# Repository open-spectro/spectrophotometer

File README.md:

# Learning spectrophotometry

## Introduction

You can find very expensive and powerful 
spectrophotometer on the market but for teaching they are most
of the time a black box that can not be open.

In order to be able to better teach the technique we would
like to create a simple, open source, spectrophotometer.

The idea is relatively simple. You have 4 leds (red, green,
blue, white) that can be turned on / off. The beam will
cross a cell, go through a slit and is diffracted using a
grating film.

A linear sensor allows to analyze the intensity of each
resulting wavelength.

There are 4 main parts in this project
* the electronic and microcontroller
* the microcontroller firmware
* the box
* the end-user graphical interface

Thanks to a google chrome "apps" it is possible directly from the web-browser to control the instrument. The application is available for [free on the store](https://chrome.google.com/webstore/detail/open-spectrophotometer/bmkhbnoonjkmdlkfncokjkanfgilppkn).

## Electronic and microcontroller

We played for a while with the Arduino platform and quickly
found out that you can relatively easily create your own
board that is compatible with the Arduino software.

This means that all the electronic can be designed to fit
exactly your needs but you will still be able to program
the device using the [Arduino](http://www.arduino.cc/).

The linear sensor is based on the linear sensor array 
[TSL1402R](http://ams.com/content/download/250165/975693/TSL1402R_Datasheet_EN_v1.pdf).

### Buttons

In order to prevent any problems with mechanical buttons and
buttons on the service, capasitive sensors are considered.

http://playground.arduino.cc/Main/CapacitiveSensor?from=Main.CapSense

## Firmware

The device emulates an Arduino Leonardo and can therefore be
programmed using the USB cable using the
[Arduino software](http://www.arduino.cc/en/Main/Software). We 
currently use version 1.0.6.

The first tie the bootloader has to be installed on the
microcontroller ATMega32U4.

## The box

To create the box we are using:
* [123D design](http://www.123dapp.com/design)
* [Robox 3D printer](http://www.cel-robox.com/)

## End-user graphical interface

The user interface is based on the 
[Visualizer](http://github.com/npellet/visualizer) and is available on the [Google Apps store](https://chrome.google.com/webstore/detail/open-spectrophotometer/bmkhbnoonjkmdlkfncokjkanfgilppkn)

## Control from the terminal (Advanced users)

From a terminal on the macintosh you could currently do something like

``` screen /dev/tty.usbmodemfdXXX 115200 ```

(you need to find the correct tty device using 

``` ls /dev/tty.usb* ```

To kill this session

``` CTRL + a and then k ```

You are then in the terminal menu and you can enter

```h + enter```

For the various options.

To take a spectrum:

```r + enter```

You will then have 10s (blue blinking) to put the reference sample.
Once the green flash appears you have 10s to put the sample.

All the results may be pasted in a view:

http://www.cheminfo.org/Spectra/Spectrophotometer/Test.html

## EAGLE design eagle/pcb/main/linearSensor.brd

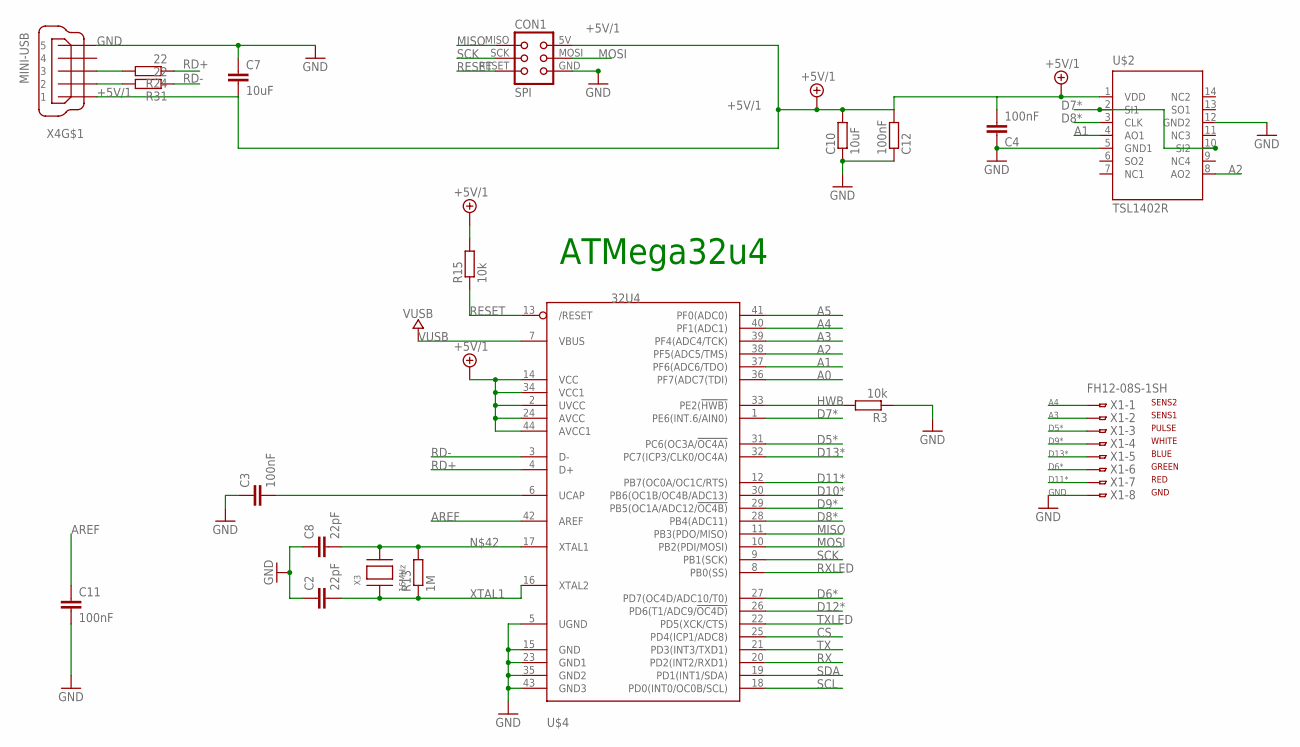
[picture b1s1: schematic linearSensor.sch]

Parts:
C2, C8: 22pF; C0805K
C3, C11: 100nF; C0805K
C4: 100nF; C0805
C7: 10uF; C0805
C10: 10uF; M0805
C12: 100nF; M0805
CON1: SPI; TC2030-MCP-NL
R3, R15: 10k; M0805
R13: 1M; M0805
R24, R31: 22; M0805
U$2: TSL1402R; DIL14
U$4: 32U4; TQFP44
X1: FH12-08S-1SH
X3: 16MHz; NX6035
X4: MINI-USB; 32005-201

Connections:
+5V/1: C4.2, C7.2, C10.2, C12.2, CON1.5V (VCC), R15.2, U$2.1 (VDD), U$4.2 (UVCC), U$4.14 (VCC), U$4.24 (AVCC), U$4.34 (VCC1), U$4.44 (AVCC1), X4.1
A0: U$4.36 (PF7(ADC7(TDI))
A1: U$2.4 (AO1), U$4.37 (PF6(ADC6/TDO))
A2: U$2.8 (AO2), U$4.38 (PF5(ADC5/TMS))
A3: U$4.39 (PF4(ADC4/TCK)), X1.2
A4: U$4.40 (PF1(ADC1)), X1.1
A5: U$4.41 (PF0(ADC0))
AREF: C11.1, U$4.42 (AREF)
CS: U$4.25 (PD4(ICP1/ADC8))
D5*: U$4.31 (PC6(OC3A/!OC4A)), X1.3
D6*: U$4.27 (PD7(OC4D/ADC10/T0)), X1.6
D7*: U$2.2 (SI1), U$2.10 (SI2), U$4.1 (PE6(INT.6/AIN0))
D8*: U$2.3 (CLK), U$4.28 (PB4(ADC11))
D9*: U$4.29 (PB5(OC1A/ADC12/!OC4B)), X1.4
D10*: U$4.30 (PB6(OC1B/OC4B/ADC13))
D11*: U$4.12 (PB7(OC0A/OC1C/RTS)), X1.7
D12*: U$4.26 (PD6(T1/ADC9/!OC4D))
D13*: U$4.32 (PC7(ICP3/CLK0/OC4A)), X1.5
D_USB+: R24.2, X4.3
D_USB-: R31.2, X4.2
GND: C2.1, C3.1, C4.1, C7.1, C8.1, C10.1, C11.2, C12.1, CON1.GND, R3.1, U$2.5 (GND1), U$2.12 (GND2), U$4.5 (UGND), U$4.15 (GND), U$4.23 (GND1), U$4.35 (GND2), U$4.43 (GND3), X1.8, X4.5
HWB: R3.2, U$4.33 (PE2(!HWB))
MISO: CON1.MISO, U$4.11 (PB3(PDO/MISO))
MOSI: CON1.MOSI, U$4.10 (PB2(PDI/MOSI))
unnamed: C3.2, U$4.6 (UCAP)
unnamed: C8.2, R13.2, U$4.17 (XTAL1), X3.P$2
RD+: R24.1, U$4.4 (D+)
RD-: R31.1, U$4.3 (D-)
RESET: CON1.RESET, R15.1, U$4.13 (/RESET)
RX: U$4.20 (PD2(INT2/RXD1))
RXLED: U$4.8 (PB0(SS))
SCK: CON1.SCK, U$4.9 (PB1(SCK))
SCL: U$4.18 (PD0(INT0/OC0B/SCL))
SDA: U$4.19 (PD1(INT1/SDA))
TX: U$4.21 (PD3(INT3/TXD1))
TXLED: U$4.22 (PD5(XCK/CTS))
VUSB: U$4.7 (VBUS)
XTAL1: C2.2, R13.1, U$4.16 (XTAL2), X3.P$1

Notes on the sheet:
ATMega32u4
GND
RED
GREEN
BLUE
WHITE
PULSE
SENS1
SENS2

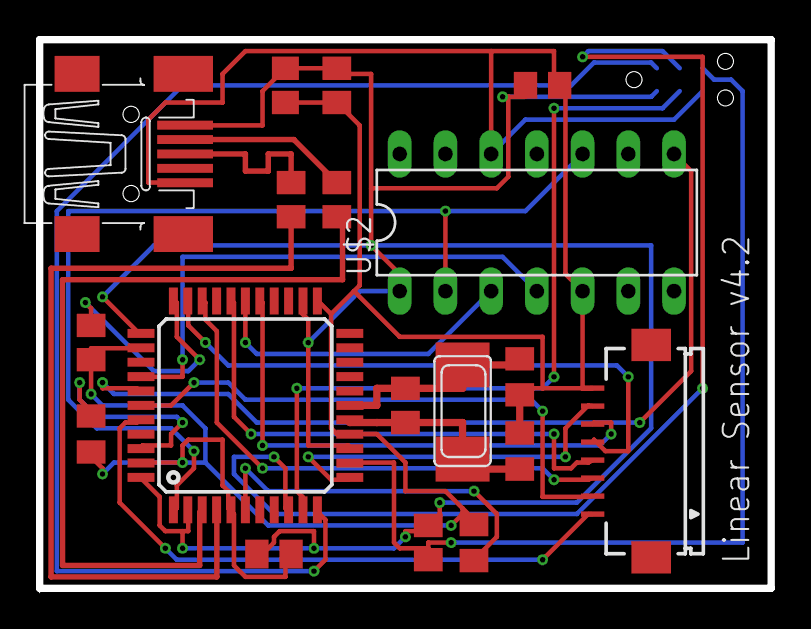
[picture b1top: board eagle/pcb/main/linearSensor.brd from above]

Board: 2 copper layers, 40.6 x 30.5 mm, 19 parts (1 on the bottom side), 26 nets.

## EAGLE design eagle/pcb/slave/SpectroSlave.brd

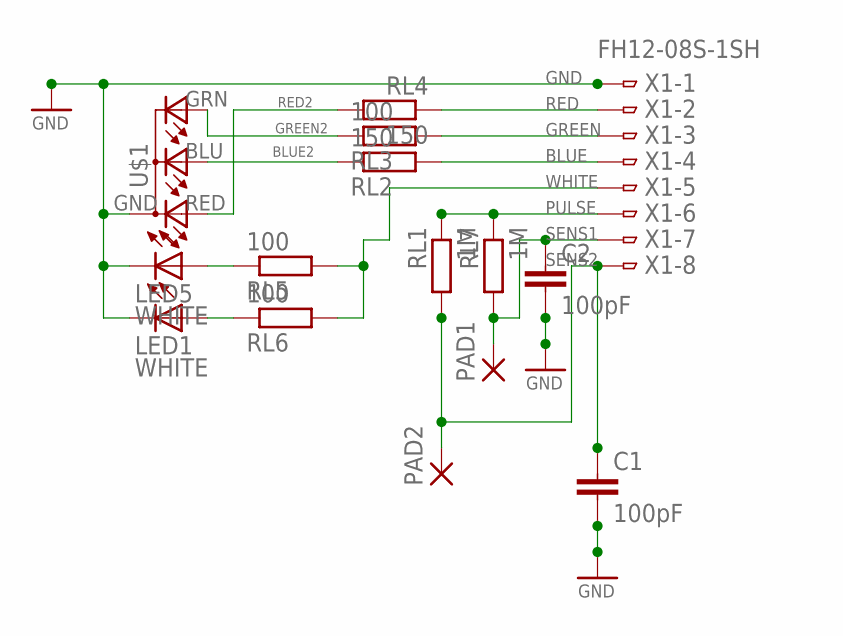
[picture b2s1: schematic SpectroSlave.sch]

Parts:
C1, C2: 100pF; C0805
LED1, LED5: WHITE; LED3MM
PAD1, PAD2: SMD5; SMD2,54-5,08
RL1, RL7: 1M; R0805
RL2, RL4: 150; R0805
RL3, RL5, RL6: 100; R0805
U$1: RGB-COMMON-CATHODE; LED-TRICOLOR-THROUGHHOLE
X1: FH12-08S-1SH

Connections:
BLUE: RL2.2, X1.4
BLUE2: RL2.1, U$1.BLU (CBLUE)
GND: C1.2, C2.2, LED1.K (C), LED5.K (C), U$1.GND (A2), X1.1
GREEN: RL3.2, X1.3
GREEN2: RL3.1, U$1.GRN (CGREEN)
unnamed: LED5.A, RL5.1
unnamed: LED1.A, RL6.1
PULSE: RL1.1, RL7.1, X1.6
RED: RL4.1, X1.2
RED2: RL4.2, U$1.RED (CRED)
SENS1: C2.1, PAD1.1, RL7.2, X1.7
SENS2: C1.1, PAD2.1, RL1.2, X1.8
WHITE: RL5.2, RL6.2, X1.5

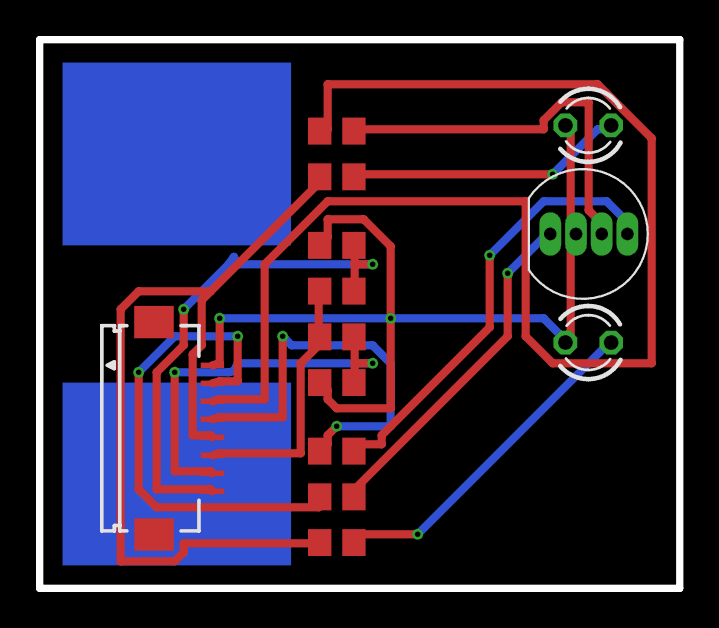
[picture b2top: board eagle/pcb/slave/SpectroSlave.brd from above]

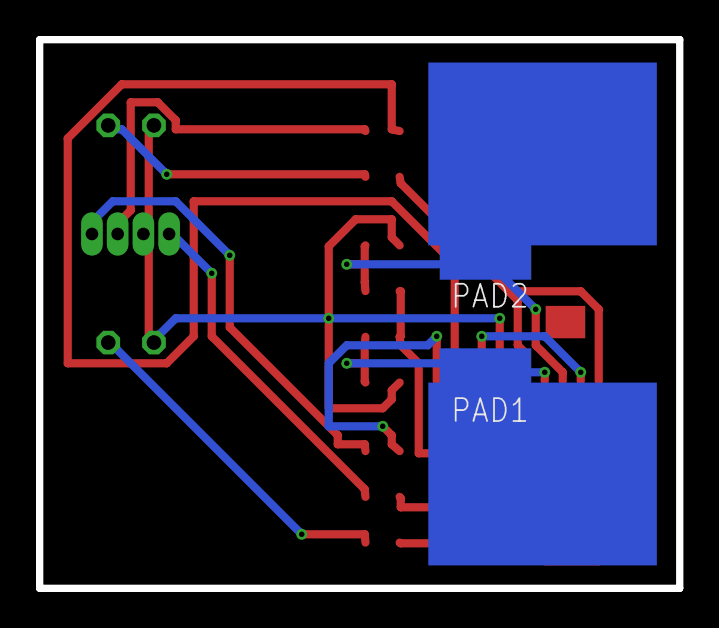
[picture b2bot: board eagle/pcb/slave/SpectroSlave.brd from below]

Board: 2 copper layers, 35.6 x 30.5 mm, 15 parts (2 on the bottom side), 13 nets.

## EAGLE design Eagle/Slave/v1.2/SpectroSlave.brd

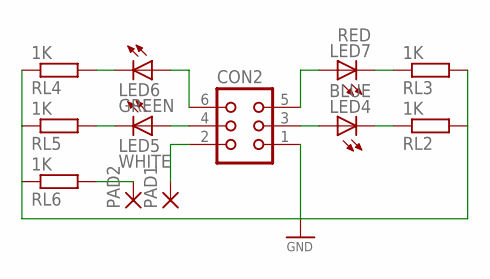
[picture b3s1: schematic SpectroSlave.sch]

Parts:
CON2: CON06L
LED4: BLUE; LED3MM
LED5: WHITE; LED3MM
LED6: GREEN; LED3MM
LED7: RED; LED3MM
PAD1, PAD2: SMD5; SMD2,54-5,08
RL2, RL3, RL4, RL5, RL6: 1K; R0805

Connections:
GND: CON2.1, RL2.2, RL3.2, RL4.1, RL5.1, RL6.1
unnamed: CON2.4, LED5.A
unnamed: CON2.6, LED6.A
unnamed: LED6.K (C), RL4.2
unnamed: CON2.2, PAD1.1
unnamed: LED7.K (C), RL3.1
unnamed: LED4.K (C), RL2.1
unnamed: CON2.3, LED4.A
unnamed: PAD2.1, RL6.2
unnamed: CON2.5, LED7.A
unnamed: LED5.K (C), RL5.2

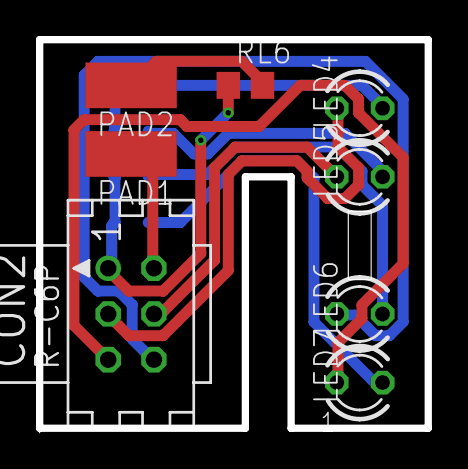
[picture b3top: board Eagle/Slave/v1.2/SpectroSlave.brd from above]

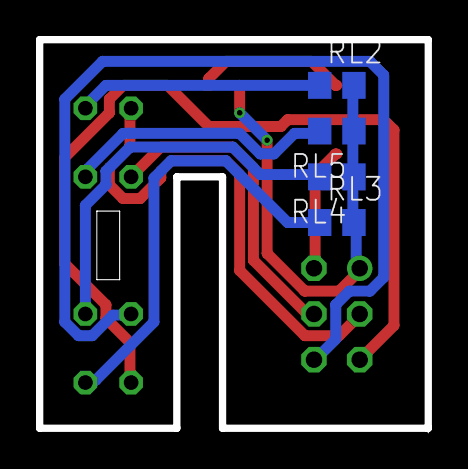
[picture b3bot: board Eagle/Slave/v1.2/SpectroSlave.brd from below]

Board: 2 copper layers, 21.6 x 21.6 mm, 12 parts (4 on the bottom side), 11 nets.

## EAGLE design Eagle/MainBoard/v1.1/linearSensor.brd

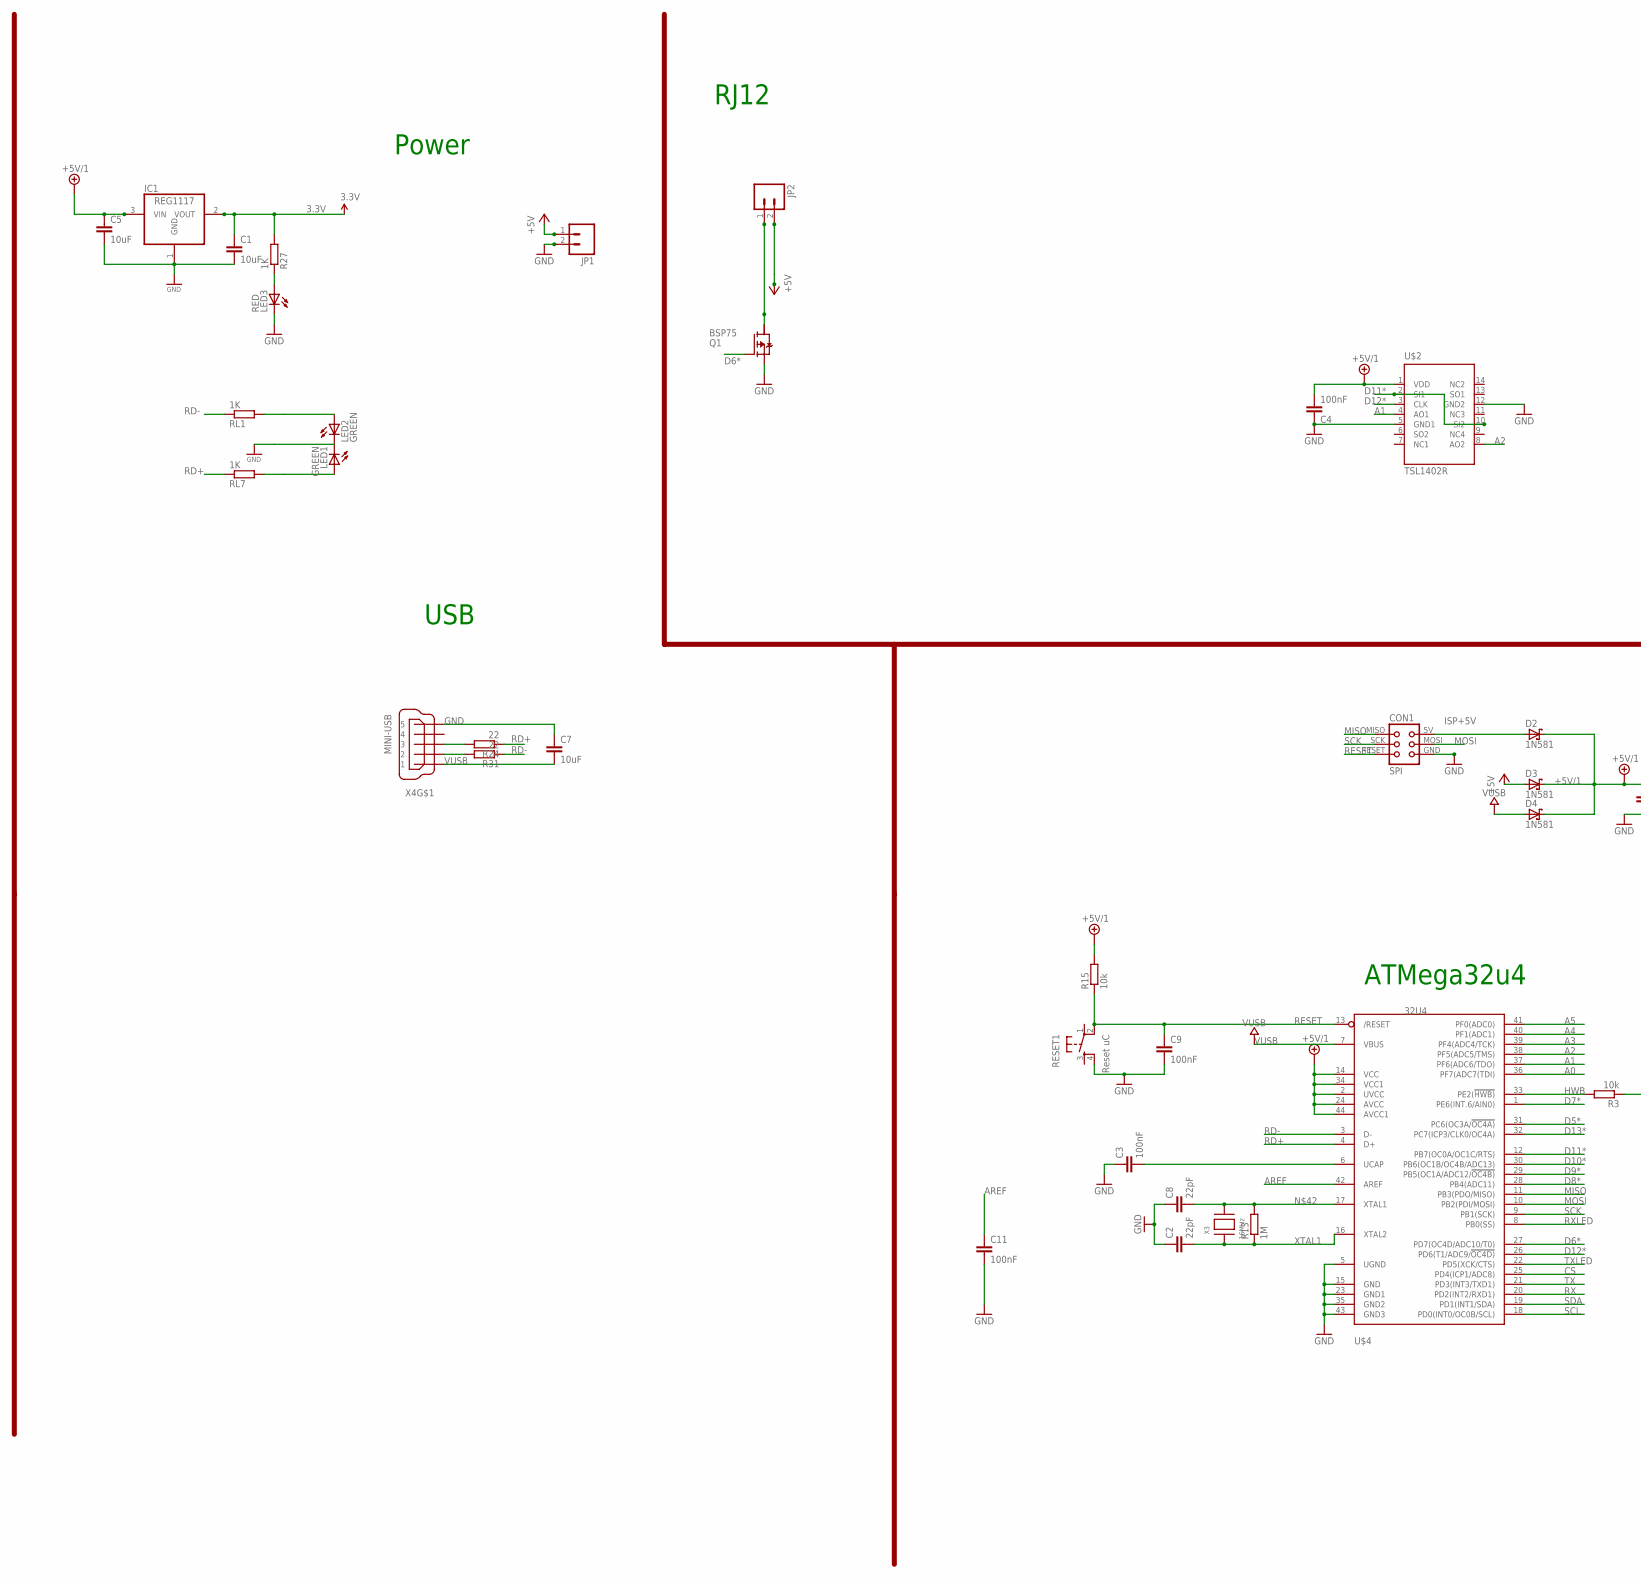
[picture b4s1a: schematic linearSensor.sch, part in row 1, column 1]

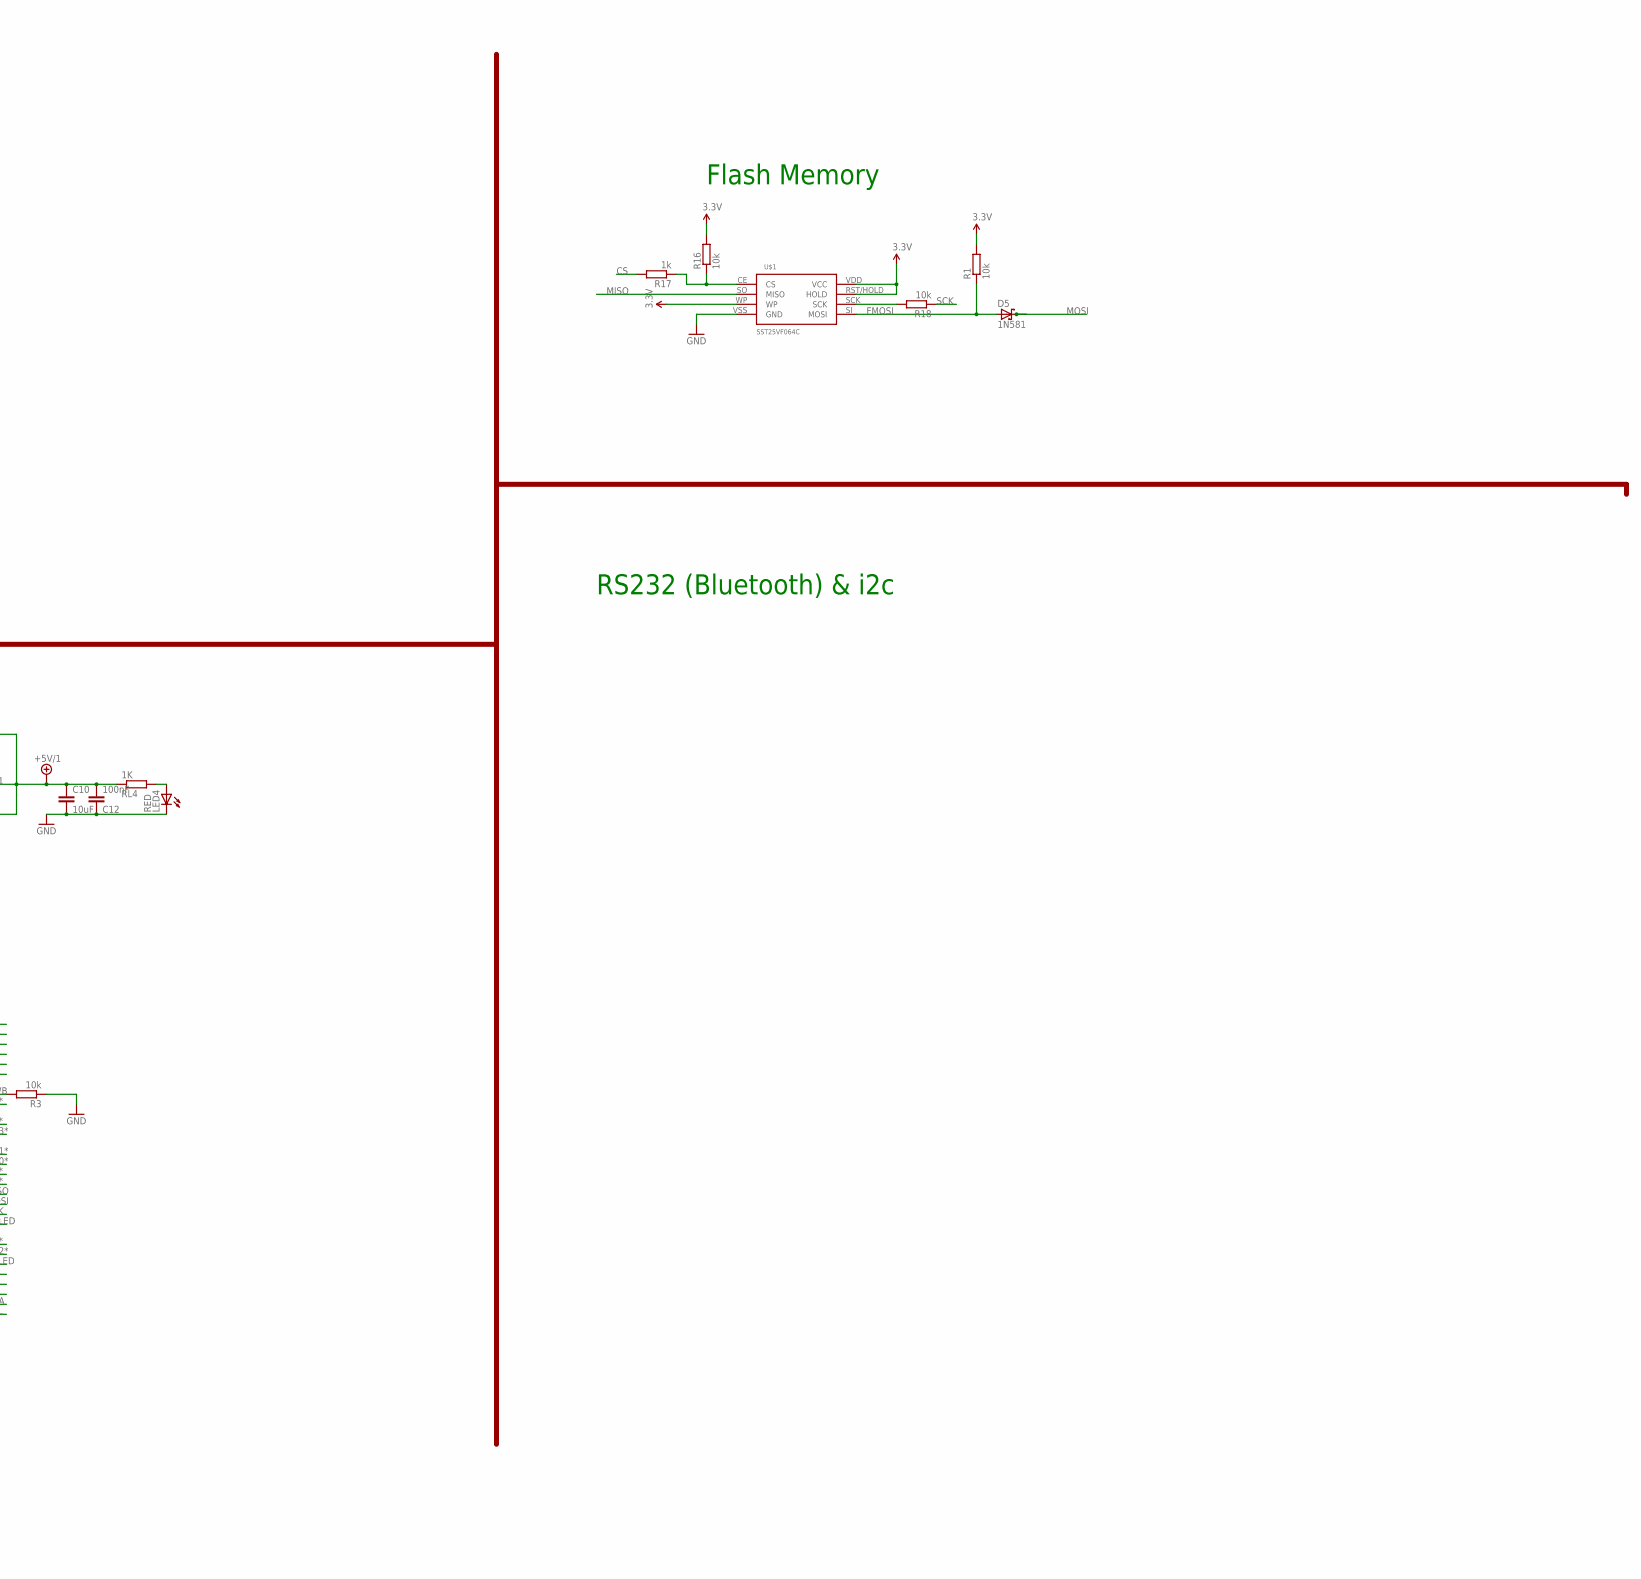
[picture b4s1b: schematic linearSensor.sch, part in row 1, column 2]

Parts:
C1, C5, C7, C10: 10uF; C1206
C2, C8: 22pF; C1206
C3, C4, C9, C11, C12: 100nF; C1206
CON1: SPI; TC2030-MCP-NL
D2, D3, D4, D5: 1N581; LED-1206
IC1: REG1117; SOT223
JP1, JP2: M02LOCK_LONGPADS; 1X02_LOCK_LONGPADS
LED1, LED2: GREEN; CHIP-LED0805
LED3, LED4: RED; CHIP-LED0805
Q1: BSP75; PG-SOT-223
R1, R16, R18: 10k; R1206
R3, R15: 10k; M0805
R13: 1M; R1206
R17: 1k; R0805
R24, R31: 22; M1206
R27: 1K; R0805
RESET1: Reset uC; TACTILE_SWITCH_SMD
RL1, RL4, RL7: 1K; R0805
U$1: SST25VF064C; SOIC_8-LEAD
U$2: TSL1402R; DIL14
U$4: 32U4; TQFP44
X3: 16MHz; NX6035
X4: MINI-USB; 32005-201

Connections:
3.3V: C1.1, IC1.2 (VOUT), R1.2, R16.2, R27.2, U$1.RST/HOLD (HOLD), U$1.VDD (VCC), U$1.WP
+5V: D3.A, JP1.1, JP2.2
+5V/1: C4.2, C5.1, C10.1, C12.2, D2.C, D3.C, D4.C, IC1.3 (VIN), R15.2, RL4.1, U$2.1 (VDD), U$4.2 (UVCC), U$4.14 (VCC), U$4.24 (AVCC), U$4.34 (VCC1), U$4.44 (AVCC1)
A0: U$4.36 (PF7(ADC7(TDI))
A1: U$2.4 (AO1), U$4.37 (PF6(ADC6/TDO))
A2: U$2.8 (AO2), U$4.38 (PF5(ADC5/TMS))
A3: U$4.39 (PF4(ADC4/TCK))
A4: U$4.40 (PF1(ADC1))
A5: U$4.41 (PF0(ADC0))
AREF: C11.1, U$4.42 (AREF)
CS: R17.2, U$4.25 (PD4(ICP1/ADC8))
D5*: U$4.31 (PC6(OC3A/!OC4A))
D6*: Q1.1 (G), U$4.27 (PD7(OC4D/ADC10/T0))
D7*: U$4.1 (PE6(INT.6/AIN0))
D8*: U$4.28 (PB4(ADC11))
D9*: U$4.29 (PB5(OC1A/ADC12/!OC4B))
D10*: U$4.30 (PB6(OC1B/OC4B/ADC13))
D11*: U$2.2 (SI1), U$2.10 (SI2), U$4.12 (PB7(OC0A/OC1C/RTS))
D12*: U$2.3 (CLK), U$4.26 (PD6(T1/ADC9/!OC4D))
D13*: U$4.32 (PC7(ICP3/CLK0/OC4A))
D+USB: R24.2, X4.3
D-USB: R31.2, X4.2
FMOSI: D5.A, R1.1, U$1.SI (MOSI)
GND: C1.2, C2.1, C3.1, C4.1, C5.2, C7.1, C8.1, C9.2, C10.2, C11.2, C12.1, CON1.GND, IC1.1 (GND), JP1.2, LED1.C, LED2.C, LED3.C, LED4.C, Q1.3 (S), R3.1, RESET1.4, U$1.VSS (GND), U$2.5 (GND1), U$2.12 (GND2), U$4.5 (UGND), U$4.15 (GND), U$4.23 (GND1), U$4.35 (GND2), U$4.43 (GND3), X4.5
HWB: R3.2, U$4.33 (PE2(!HWB))
ISP+5V: CON1.5V (VCC), D2.A
MISO: CON1.MISO, U$1.SO (MISO), U$4.11 (PB3(PDO/MISO))
MOSI: CON1.MOSI, D5.C, U$4.10 (PB2(PDI/MOSI))
unnamed: LED2.A, RL1.2
unnamed: R16.1, R17.1, U$1.CE (CS)
unnamed: LED4.A, RL4.2
unnamed: LED1.A, RL7.2
unnamed: C3.2, U$4.6 (UCAP)
unnamed: LED3.A, R27.1
unnamed: R18.2, U$1.SCK
unnamed: JP2.1, Q1.2 (D)
unnamed: C8.2, R13.2, U$4.17 (XTAL1), X3.P$2
RD+: R24.1, RL7.1, U$4.4 (D+)
RD-: R31.1, RL1.1, U$4.3 (D-)
RESET: C9.1, CON1.RESET, R15.1, RESET1.2, U$4.13 (/RESET)
RX: U$4.20 (PD2(INT2/RXD1))
RXLED: U$4.8 (PB0(SS))
SCK: CON1.SCK, R18.1, U$4.9 (PB1(SCK))
SCL: U$4.18 (PD0(INT0/OC0B/SCL))
SDA: U$4.19 (PD1(INT1/SDA))
TX: U$4.21 (PD3(INT3/TXD1))
TXLED: U$4.22 (PD5(XCK/CTS))
VUSB: C7.2, D4.A, U$4.7 (VBUS), X4.1
XTAL1: C2.2, R13.1, U$4.16 (XTAL2), X3.P$1

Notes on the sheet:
Flash Memory
RJ12
ATMega32u4
USB
Power
RS232 (Bluetooth) & i2c

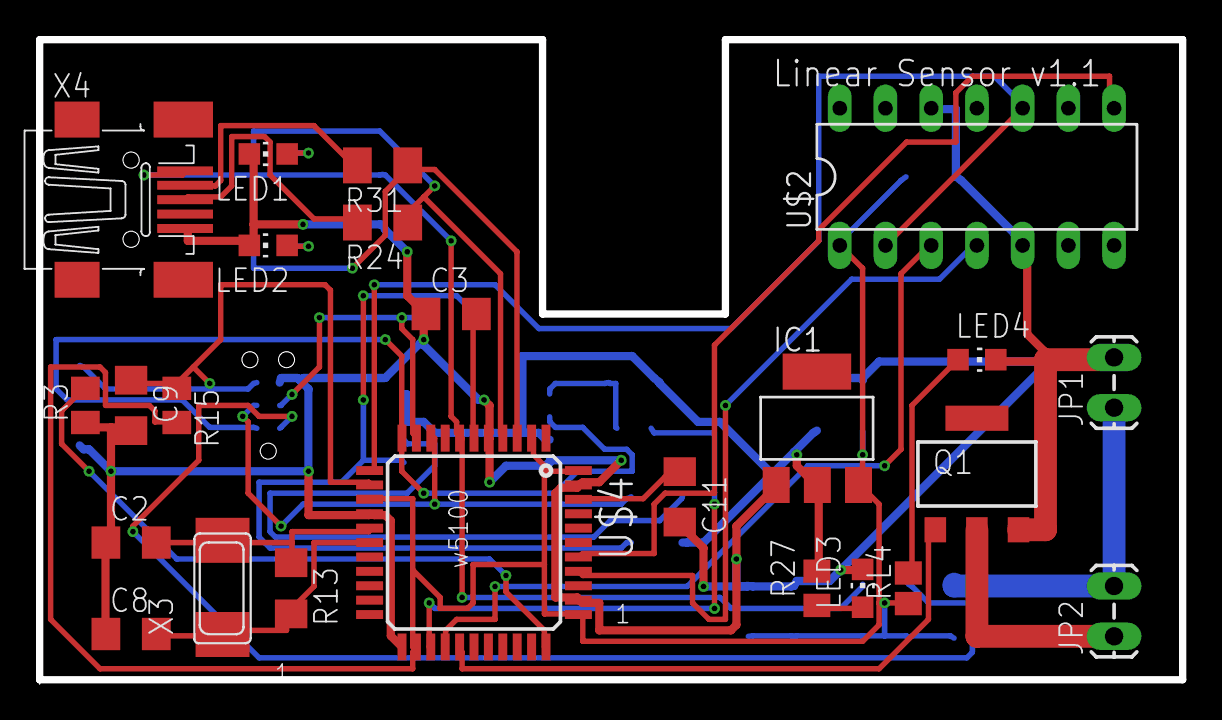
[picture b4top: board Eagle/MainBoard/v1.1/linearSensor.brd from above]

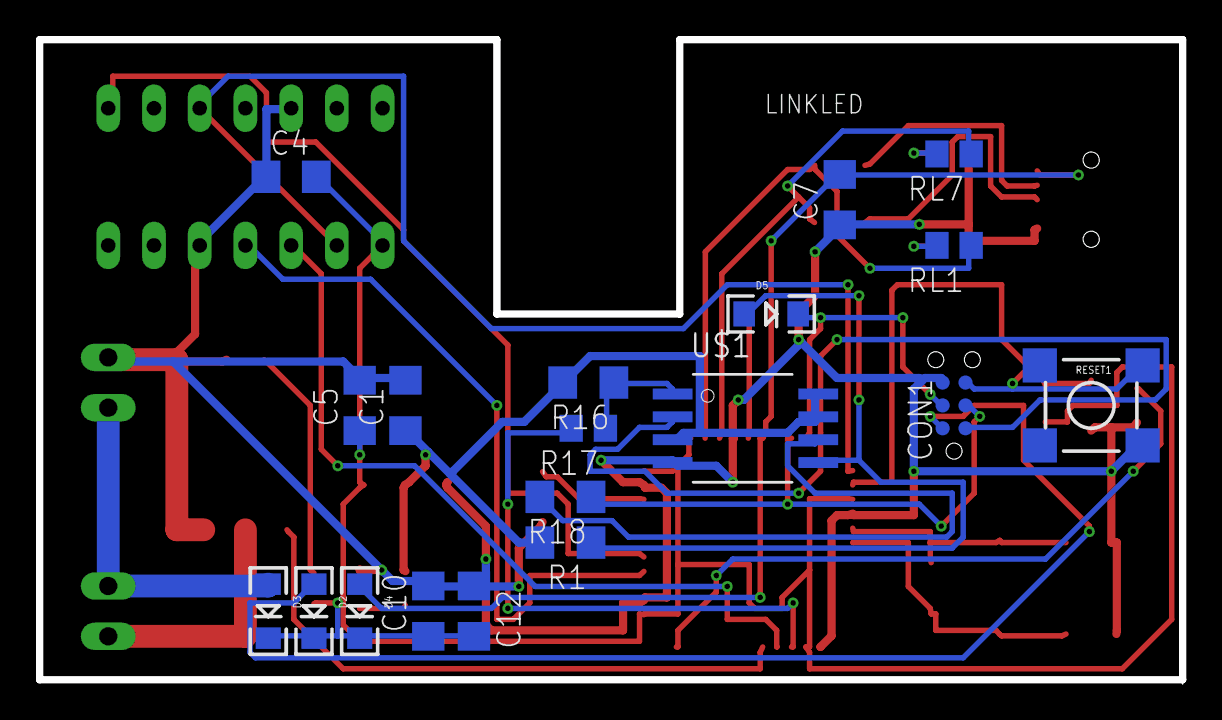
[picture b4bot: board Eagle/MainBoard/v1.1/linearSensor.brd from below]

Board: 2 copper layers, 63.5 x 35.6 mm, 43 parts (19 on the bottom side), 33 nets.

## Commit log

2014-11-15 First release
2014-11-15 Add first files
2015-05-04 Refactor the code to allow more possibilities Show linearity of the detector
2015-05-08 Add 3D model
2015-05-08 Add the cover
2015-05-10 Update code for autocallibration
2015-05-10 Update cver
2015-05-10 Add new multithread code for acquisition with menu on serial port
2015-05-10 Improve code with light show ;)
2015-05-10 Fix bugs
2015-05-16 Improve box
2015-05-18 Add double CR as delimiter between instructions
2015-05-18 create electron project
2015-05-18 proof of concept
2015-05-19 Add parameter for number of acquisition
2015-05-19 first view version
2015-05-19 add error display
2015-05-19 add config.json
2015-05-23 Add new salve and capacitive sensor sketch
2015-05-24 Add full on option
2015-08-12 Add demo files
2015-08-12 Add basic serial chrome app examples
2015-08-12 Add ingore DS_Store
2015-08-12 Fix extra space
2015-08-12 Update google example
2015-08-12 Add working example of the arduino board control
2015-08-12 Remove some console.log
2015-08-13 Publish test chrome app
2015-08-13 Update Serial to add CR LF in the answer of set parameters
2015-08-13 Create basic application with communication
2015-08-13 Create first application with communication to allow to work with visualizer.
    This version was published on google chrome store
2015-08-13 Force singleton
2015-08-13 New approach with webview
2015-08-13 Don't ask for USB access
2015-08-14 Add possibility to turn on / off leds
2015-08-14 Update spectrophotometer manifest
2015-08-14 Fix manifest
2015-08-15 New spectrophotometer board
2015-08-15 Simplify the code to have only one event
2015-08-16 Update program to deal better with double CR at the end of sending
2015-08-16 Add notification and cleanup the code
2015-08-16 Gendralising the system to many event kinds like serial, file, ...
2015-08-16 Generalizse the code to dispatch the action to each specific function like serial
2015-08-16 prepare autoconnect
2015-08-16 add sendMessage and getMessage
2015-08-17 Promise of localStorage
2015-08-17 Fully promise code and reconnect automatically on the serial port
2015-08-17 Change version
2015-08-17 Fix missing this
2015-08-17 Upadate webview for persist
2015-08-18 split the project
2017-07-08 Moved for eagle and arduino projects
2017-07-08 Add presentation files
2017-07-08 Add box
2017-08-22 add separate images

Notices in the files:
parts and their libraries:
lpatiny: ©2009 ROFA.cz - modified and updated by Robert Darlington ‹rdarlington@gmail.com›
SparkFun: Licensing: CC v3.0 Share-Alike You are welcome to use this library for commercial purposes.
